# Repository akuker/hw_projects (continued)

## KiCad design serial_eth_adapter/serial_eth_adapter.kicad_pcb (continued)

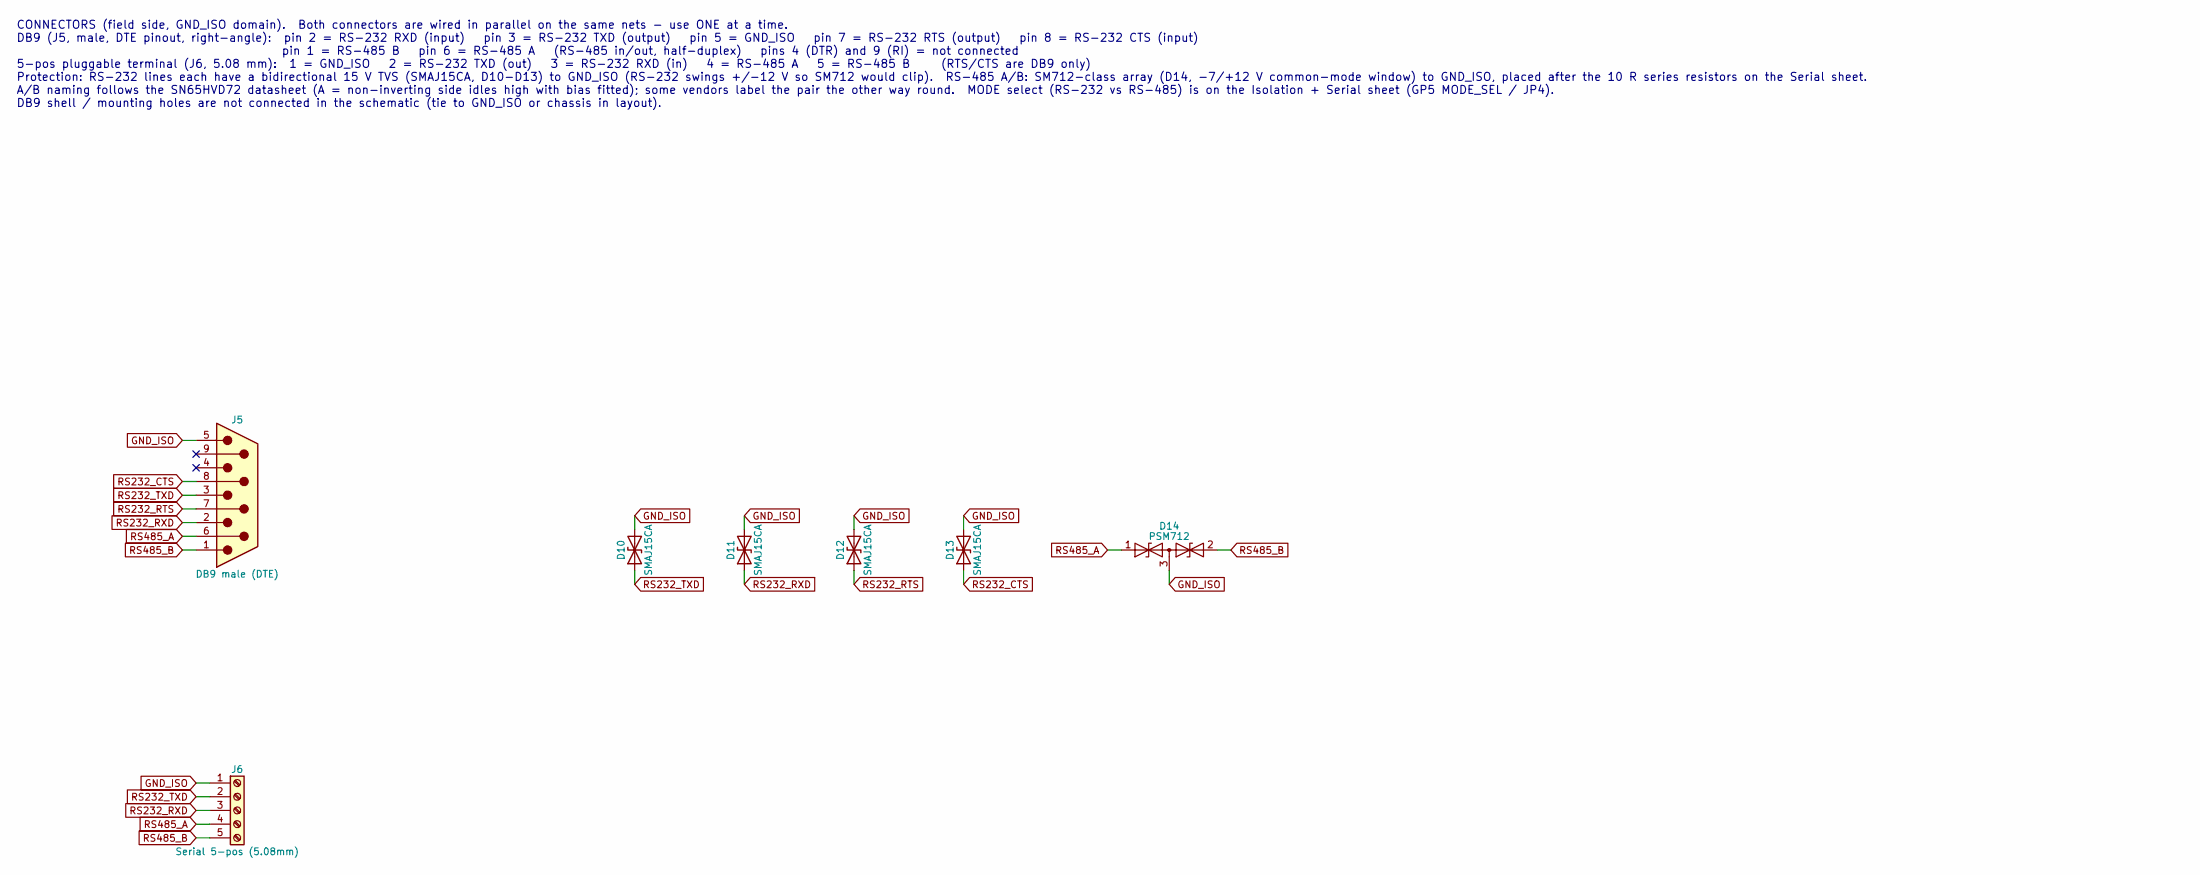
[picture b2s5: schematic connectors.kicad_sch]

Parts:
D10, D11, D12, D13: SMAJ15CA; D_SMA; MPN SMAJ15CA; LCSC C110044
D14: PSM712; SOT-23; MPN PSM712-LF-T7; LCSC C32677
J5: DB9 male (DTE); DSUB-9_Pins_Horizontal_P2.77x2.84mm_EdgePinOffset7.70mm_Hou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; MPN DS1037-09MNAKT74-0CC; LCSC C75750
J6: Serial 5-pos (5.08mm); PhoenixContact_MSTBA_2,5_5-G-5,08_1x05_P5.08mm_Horizontal; MPN KF2EDGR-5.08-5P; LCSC C441207

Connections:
GND_ISO: D10.2 (A2), D11.2 (A2), D12.2 (A2), D13.2 (A2), D14.3 (common), J5.5, J6.1; also elsewhere on the board
RS232_CTS: D13.1 (A1), J5.8; also elsewhere on the board
RS232_RTS: D12.1 (A1), J5.7; also elsewhere on the board
RS232_RXD: D11.1 (A1), J5.2, J6.3; also elsewhere on the board
RS232_TXD: D10.1 (A1), J5.3, J6.2; also elsewhere on the board
RS485_A: D14.1 (A1), J5.6, J6.4; also elsewhere on the board
RS485_B: D14.2 (A2), J5.1, J6.5; also elsewhere on the board

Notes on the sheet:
CONNECTORS (field side, GND_ISO domain). Both connectors are wired in parallel on the same nets - use ONE at a time. DB9 (J5, male, DTE pinout, right-angle): pin 2 = RS-232 RXD (input) pin 3 = RS-232 TXD (output) pin 5 = GND_ISO pin 7 = RS-232 RTS (output) pin 8 = RS-232 CTS (input) pin 1 = RS-485 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

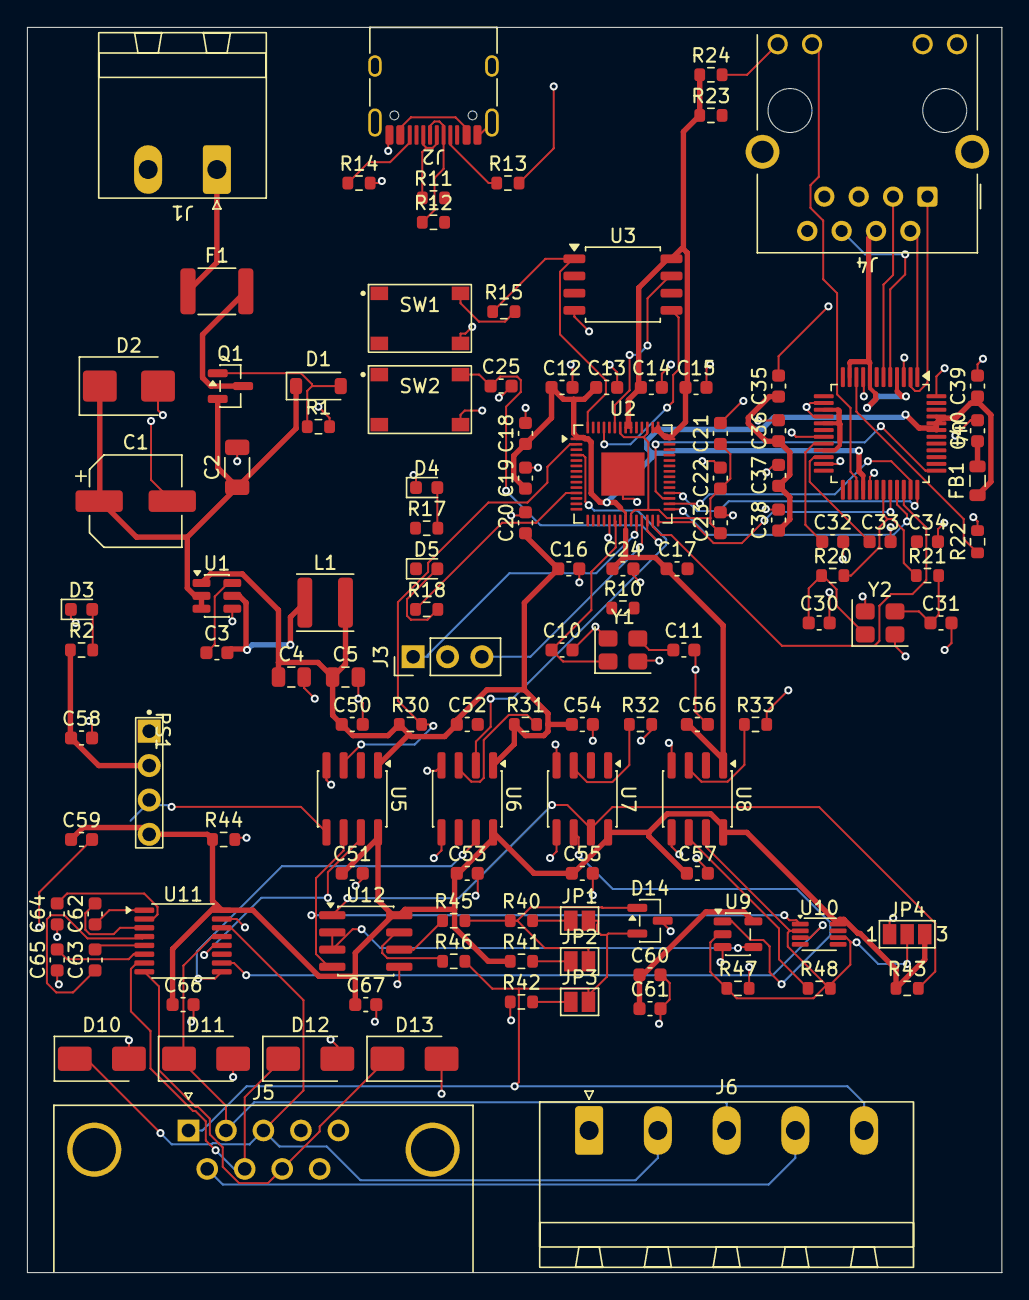
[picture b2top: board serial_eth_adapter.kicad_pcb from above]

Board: 2 copper layers, 72.0 x 92.0 mm, 119 parts (0 on the bottom side), 93 nets.

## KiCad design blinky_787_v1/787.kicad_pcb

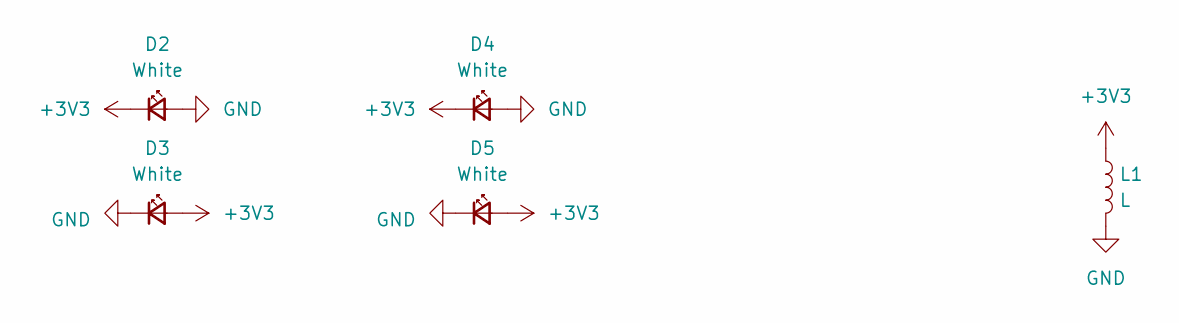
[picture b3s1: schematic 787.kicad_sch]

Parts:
D2, D3, D4, D5: White; LED_0603_1608Metric; LCSC C2290
L1: L; Coil based on ID 6

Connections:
+3V3: D2.1 (K), D3.2 (A), D4.1 (K), D5.2 (A), L1.1
GND: D2.2 (A), D3.1 (K), D4.2 (A), D5.1 (K), L1.2

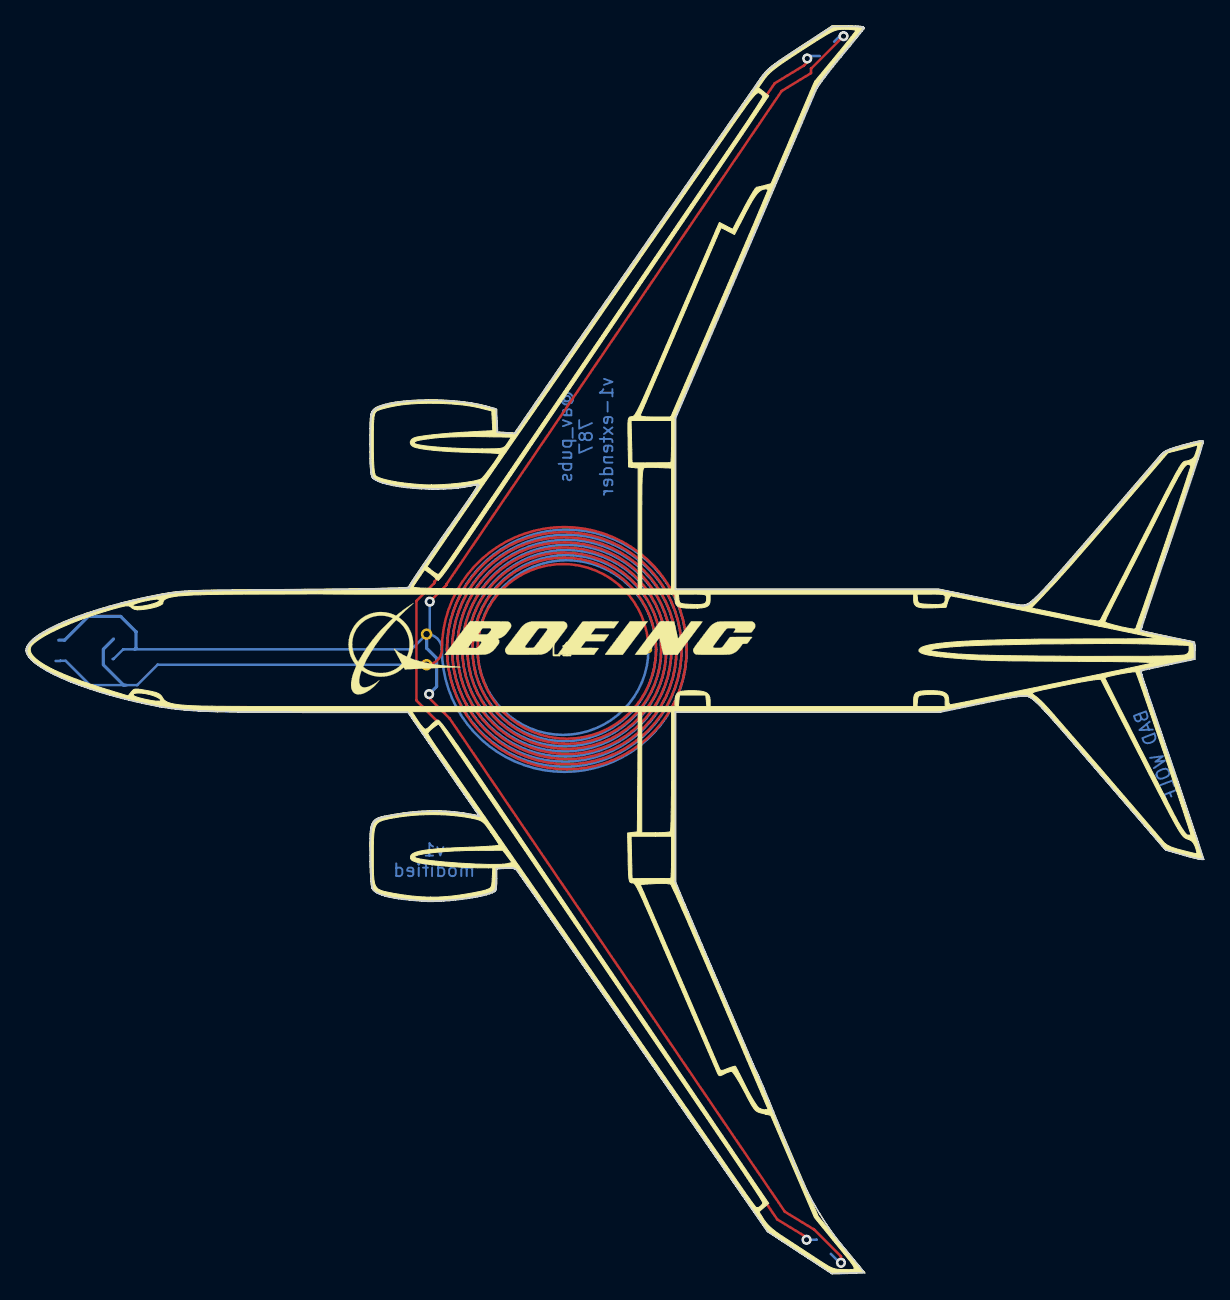
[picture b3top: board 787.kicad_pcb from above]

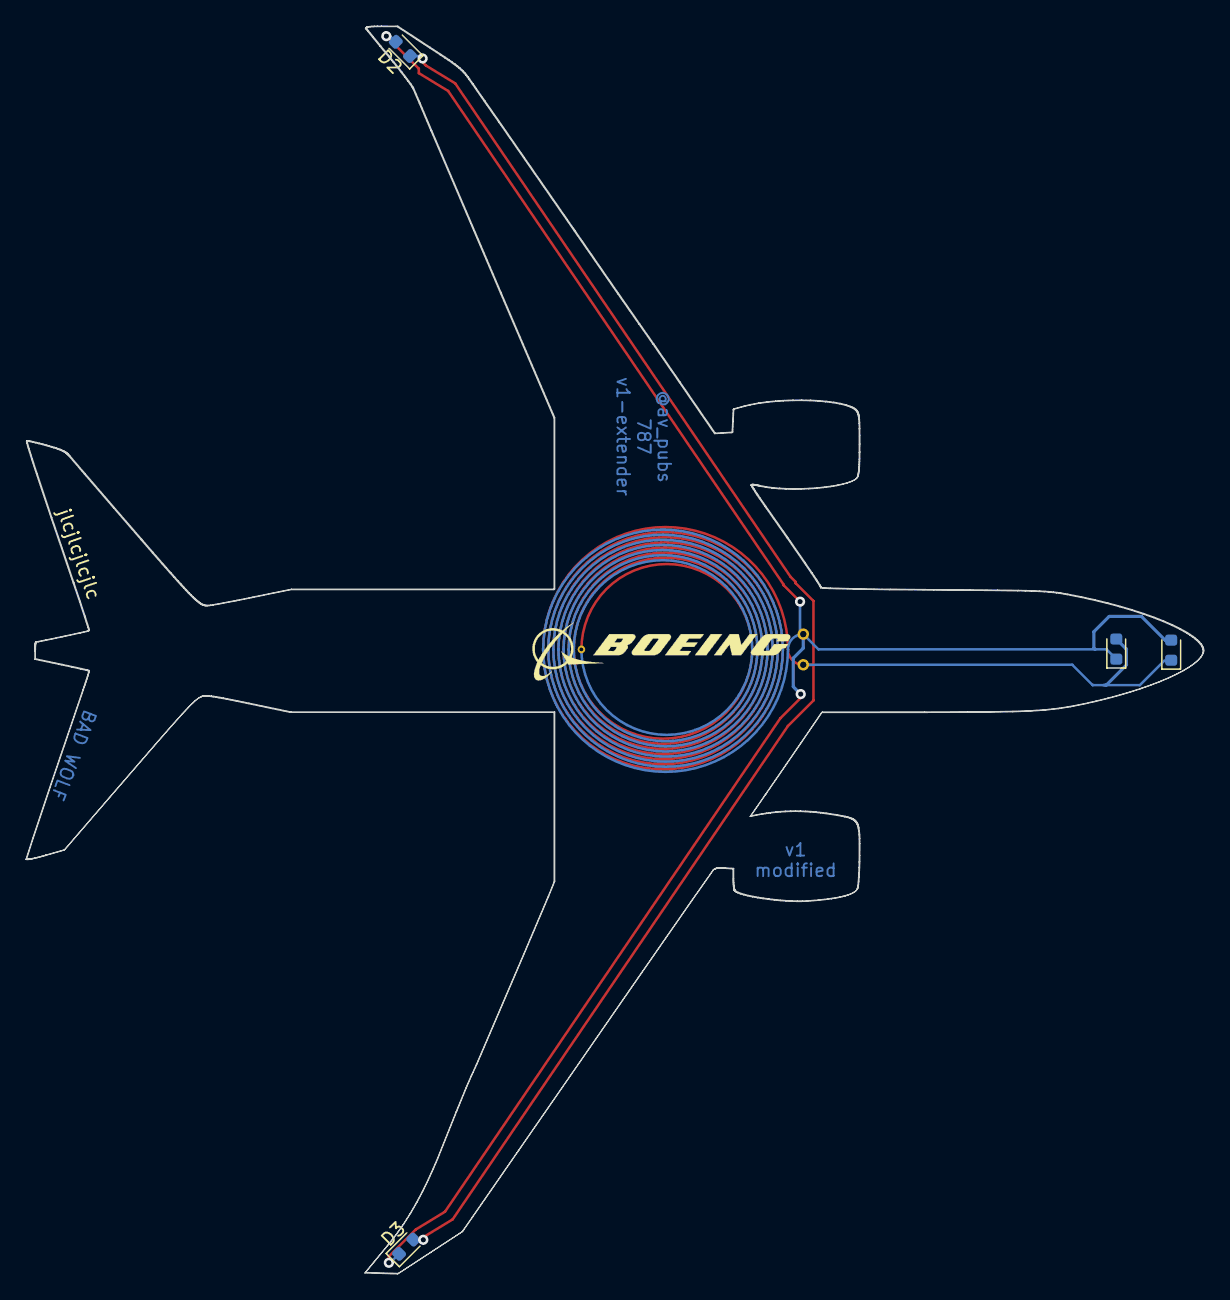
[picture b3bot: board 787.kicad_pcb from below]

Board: 2 copper layers, 92.3 x 97.8 mm, 5 parts (4 on the bottom side), 2 nets.

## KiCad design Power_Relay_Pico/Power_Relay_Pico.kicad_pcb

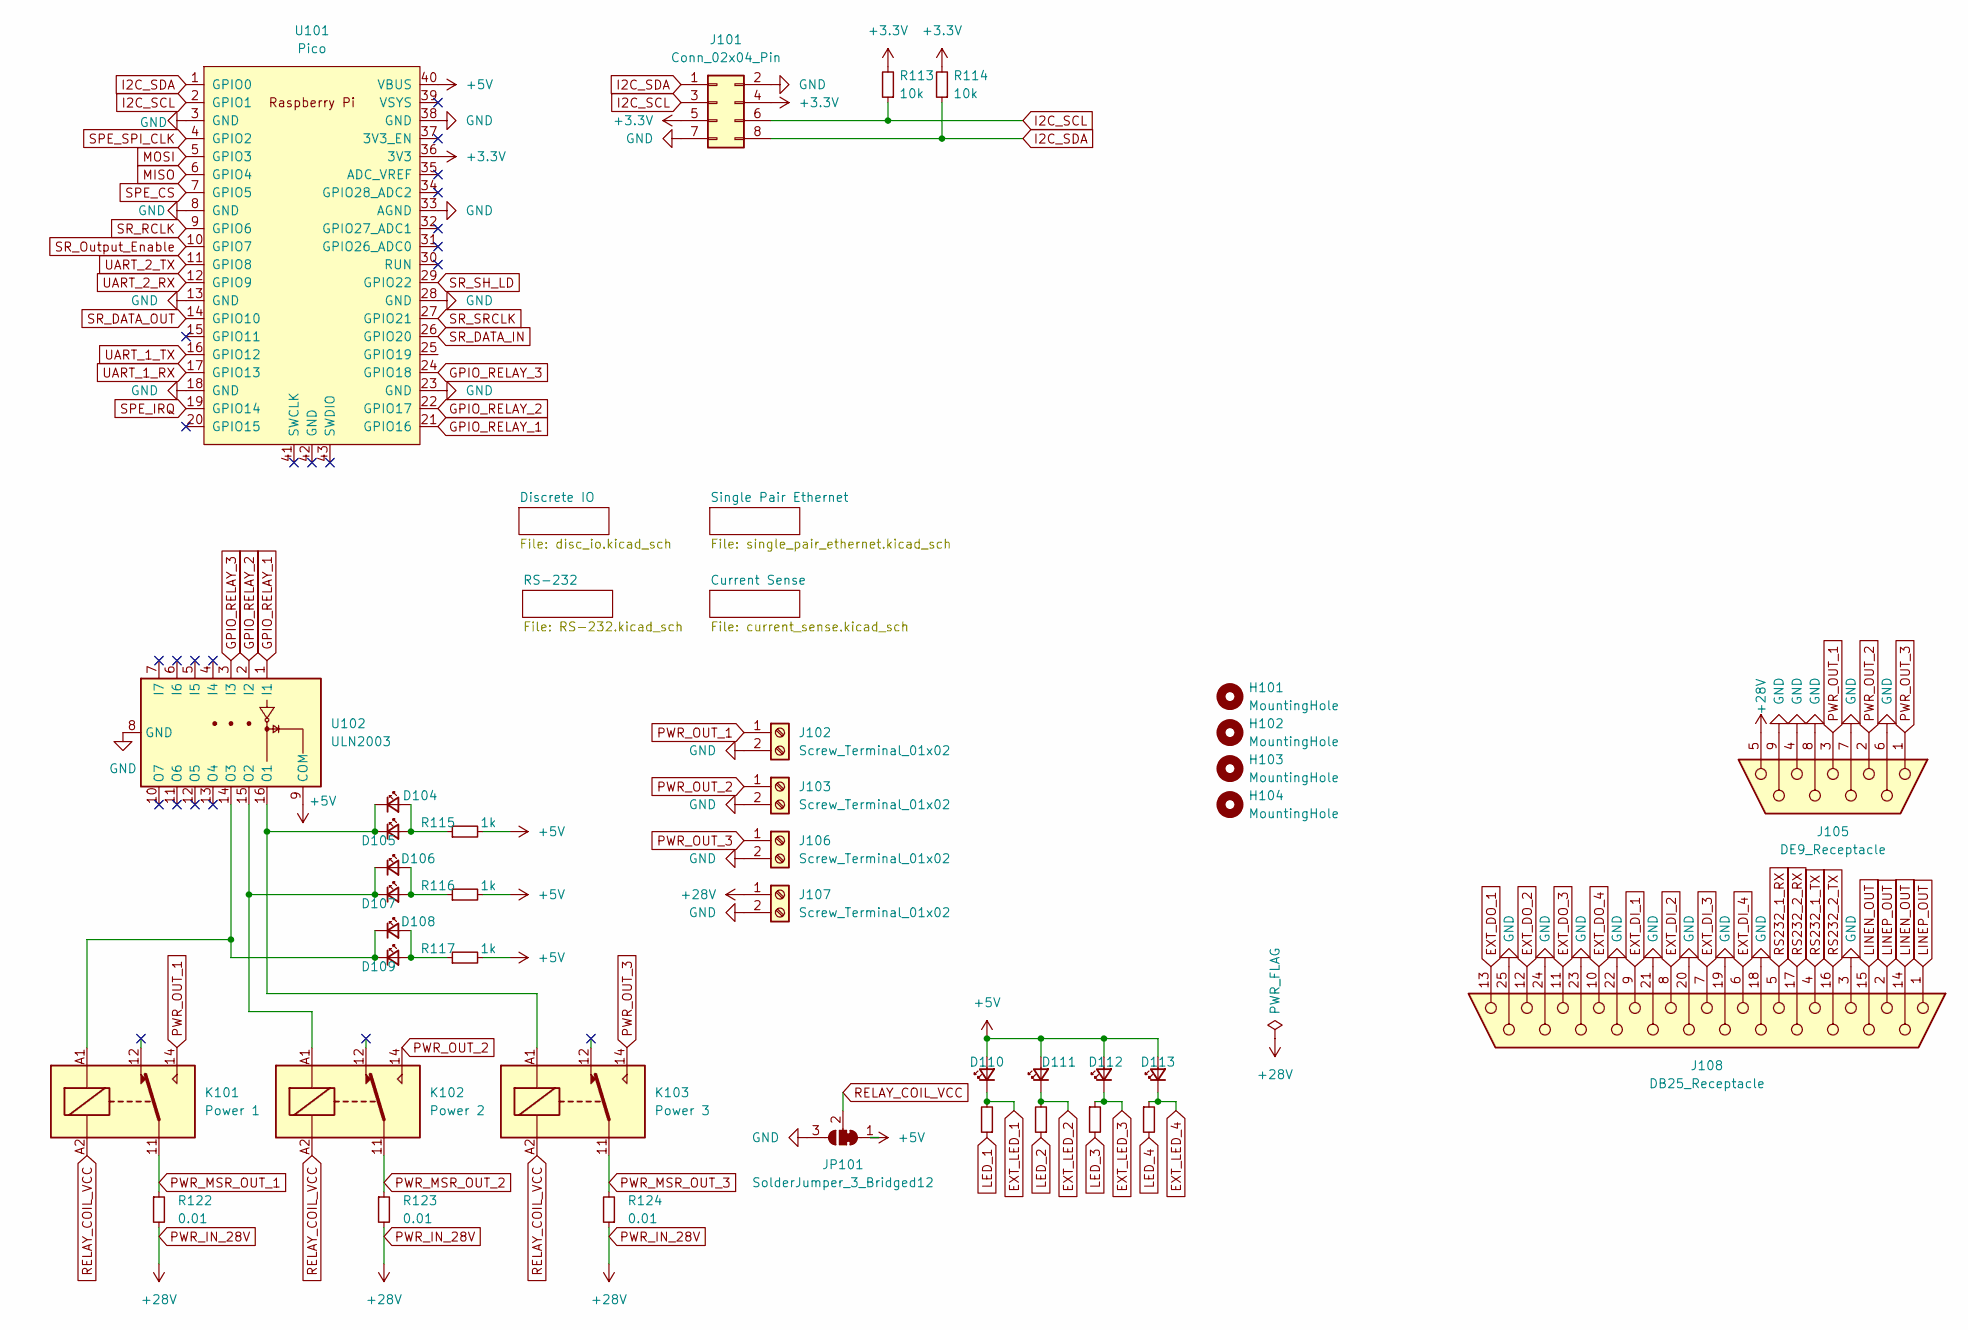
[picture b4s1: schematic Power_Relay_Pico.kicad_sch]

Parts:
D104, D106, D108: LED_Small; LED_0805_2012Metric; LCSC C2297
D105, D107, D109, D110, D111, D112, D113: LED_Small; LED_D3.0mm; LCSC --
H101, H102, H103, H104: MountingHole; MountingHole_3.2mm_M3; LCSC --
J101: Conn_02x04_Pin; PinHeader_2x04_P2.54mm_Vertical; LCSC --
J102, J103, J106, J107: Screw_Terminal_01x02; TerminalBlock_Xinya_XY308-2.54-2P_1x02_P2.54mm_Horizontal; LCSC --
J105: DE9_Receptacle; DSUB-9_Female_EdgeMount_P2.77mm; LCSC --
J108: DB25_Receptacle; DSUB-25_Female_EdgeMount_P2.77mm; LCSC --
JP101: SolderJumper_3_Bridged12; SolderJumper-3_P1.3mm_Bridged12_RoundedPad1.0x1.5mm; LCSC --
K101: Power 1; Relay_SPDT_Hongfa_HF3F-L-xx-1ZL1T; LCSC --
K102: Power 2; Relay_SPDT_Hongfa_HF3F-L-xx-1ZL1T; LCSC --
K103: Power 3; Relay_SPDT_Hongfa_HF3F-L-xx-1ZL1T; LCSC --
R113, R114: 10k; R_0603_1608Metric; LCSC C25804
R115, R116, R117, R118, R119, R120, R121: 1k; R_0603_1608Metric; LCSC C21190
R122, R123, R124: 0.01; R_1206_3216Metric; LCSC C105362
U101: Pico; RPi_Pico_SMD_TH; LCSC --
U102: ULN2003; SOIC-16_3.9x9.9mm_P1.27mm; LCSC C7512

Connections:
+3.3V: J101.4, J101.5, R113.2, R114.2, U101.36 (3V3); also elsewhere on the board
+5V: D110.2 (A), D111.2 (A), D112.2 (A), D113.2 (A), JP101.1 (A), R115.2, R116.2, R117.2, U101.40 (VBUS), U102.9 (COM); also elsewhere on the board
EXT_DI_1: J108.9; also elsewhere on the board
EXT_DI_2: J108.8; also elsewhere on the board
EXT_DI_3: J108.7; also elsewhere on the board
EXT_DI_4: J108.6; also elsewhere on the board
EXT_DO_1: J108.13; also elsewhere on the board
EXT_DO_2: J108.12; also elsewhere on the board
EXT_DO_3: J108.11; also elsewhere on the board
EXT_DO_4: J108.10; also elsewhere on the board
EXT_LED_1: D110.1 (K), R118.2
EXT_LED_2: D111.1 (K), R119.2
EXT_LED_3: D112.1 (K), R120.1
EXT_LED_4: D113.1 (K), R121.1
GND: J101.2, J101.7, J102.2, J103.2, J105.4, J105.6, J105.7, J105.8, J105.9, J106.2, J107.2, J108.3, J108.18, J108.19, J108.20, J108.21, J108.22, J108.23, J108.24, J108.25, JP101.3 (B), U101.3 (GND), U101.8 (GND), U101.13 (GND), U101.18 (GND), U101.23 (GND), U101.28 (GND), U101.33 (AGND), U101.38 (GND), U102.8 (GND); also elsewhere on the board
GPIO_RELAY_1: U101.21 (GPIO16), U102.1 (I1)
GPIO_RELAY_2: U101.22 (GPIO17), U102.2 (I2)
GPIO_RELAY_3: U101.24 (GPIO18), U102.3 (I3)
I2C_SCL: J101.3, J101.6, R113.1, U101.2 (GPIO1); also elsewhere on the board
I2C_SDA: J101.1, J101.8, R114.1, U101.1 (GPIO0); also elsewhere on the board
LED_1: R118.1; also elsewhere on the board
LED_2: R119.1; also elsewhere on the board
LED_3: R120.2; also elsewhere on the board
LED_4: R121.2; also elsewhere on the board
LINEN_OUT: J108.14, J108.15; also elsewhere on the board
LINEP_OUT: J108.1, J108.2; also elsewhere on the board
MISO: U101.6 (GPIO4); also elsewhere on the board
MOSI: U101.5 (GPIO3); also elsewhere on the board
unnamed: D104.2 (A), D105.2 (A), R115.1
unnamed: D104.1 (K), D105.1 (K), K103.A1, U102.16 (O1)
unnamed: D106.2 (A), D107.2 (A), R116.1
unnamed: D106.1 (K), D107.1 (K), K102.A1, U102.15 (O2)
unnamed: D108.2 (A), D109.2 (A), R117.1
unnamed: D108.1 (K), D109.1 (K), K101.A1, U102.14 (O3)
PWR_IN_28V: J105.5, J107.1, R122.2, R123.2, R124.1; also elsewhere on the board
PWR_MSR_OUT_1: K101.11, R122.1; also elsewhere on the board
PWR_MSR_OUT_2: K102.11, R123.1; also elsewhere on the board
PWR_MSR_OUT_3: K103.11, R124.2; also elsewhere on the board
PWR_OUT_1: J102.1, J105.3, K101.14
PWR_OUT_2: J103.1, J105.2, K102.14
PWR_OUT_3: J105.1, J106.1, K103.14
RELAY_COIL_VCC: JP101.2 (C), K101.A2, K102.A2, K103.A2
RS232_1_RX: J108.5; also elsewhere on the board
RS232_1_TX: J108.4; also elsewhere on the board
RS232_2_RX: J108.17; also elsewhere on the board
RS232_2_TX: J108.16; also elsewhere on the board
SPE_CS: U101.7 (GPIO5); also elsewhere on the board
SPE_IRQ: U101.19 (GPIO14); also elsewhere on the board
SPE_SPI_CLK: U101.4 (GPIO2); also elsewhere on the board
SR_DATA_IN: U101.26 (GPIO20); also elsewhere on the board
SR_DATA_OUT: U101.14 (GPIO10); also elsewhere on the board
SR_Output_Enable: U101.10 (GPIO7); also elsewhere on the board
SR_RCLK: U101.9 (GPIO6); also elsewhere on the board
SR_SH_LD: U101.29 (GPIO22); also elsewhere on the board
SR_SRCLK: U101.27 (GPIO21); also elsewhere on the board
UART_1_RX: U101.17 (GPIO13); also elsewhere on the board
UART_1_TX: U101.16 (GPIO12); also elsewhere on the board
UART_2_RX: U101.12 (GPIO9); also elsewhere on the board
UART_2_TX: U101.11 (GPIO8); also elsewhere on the board

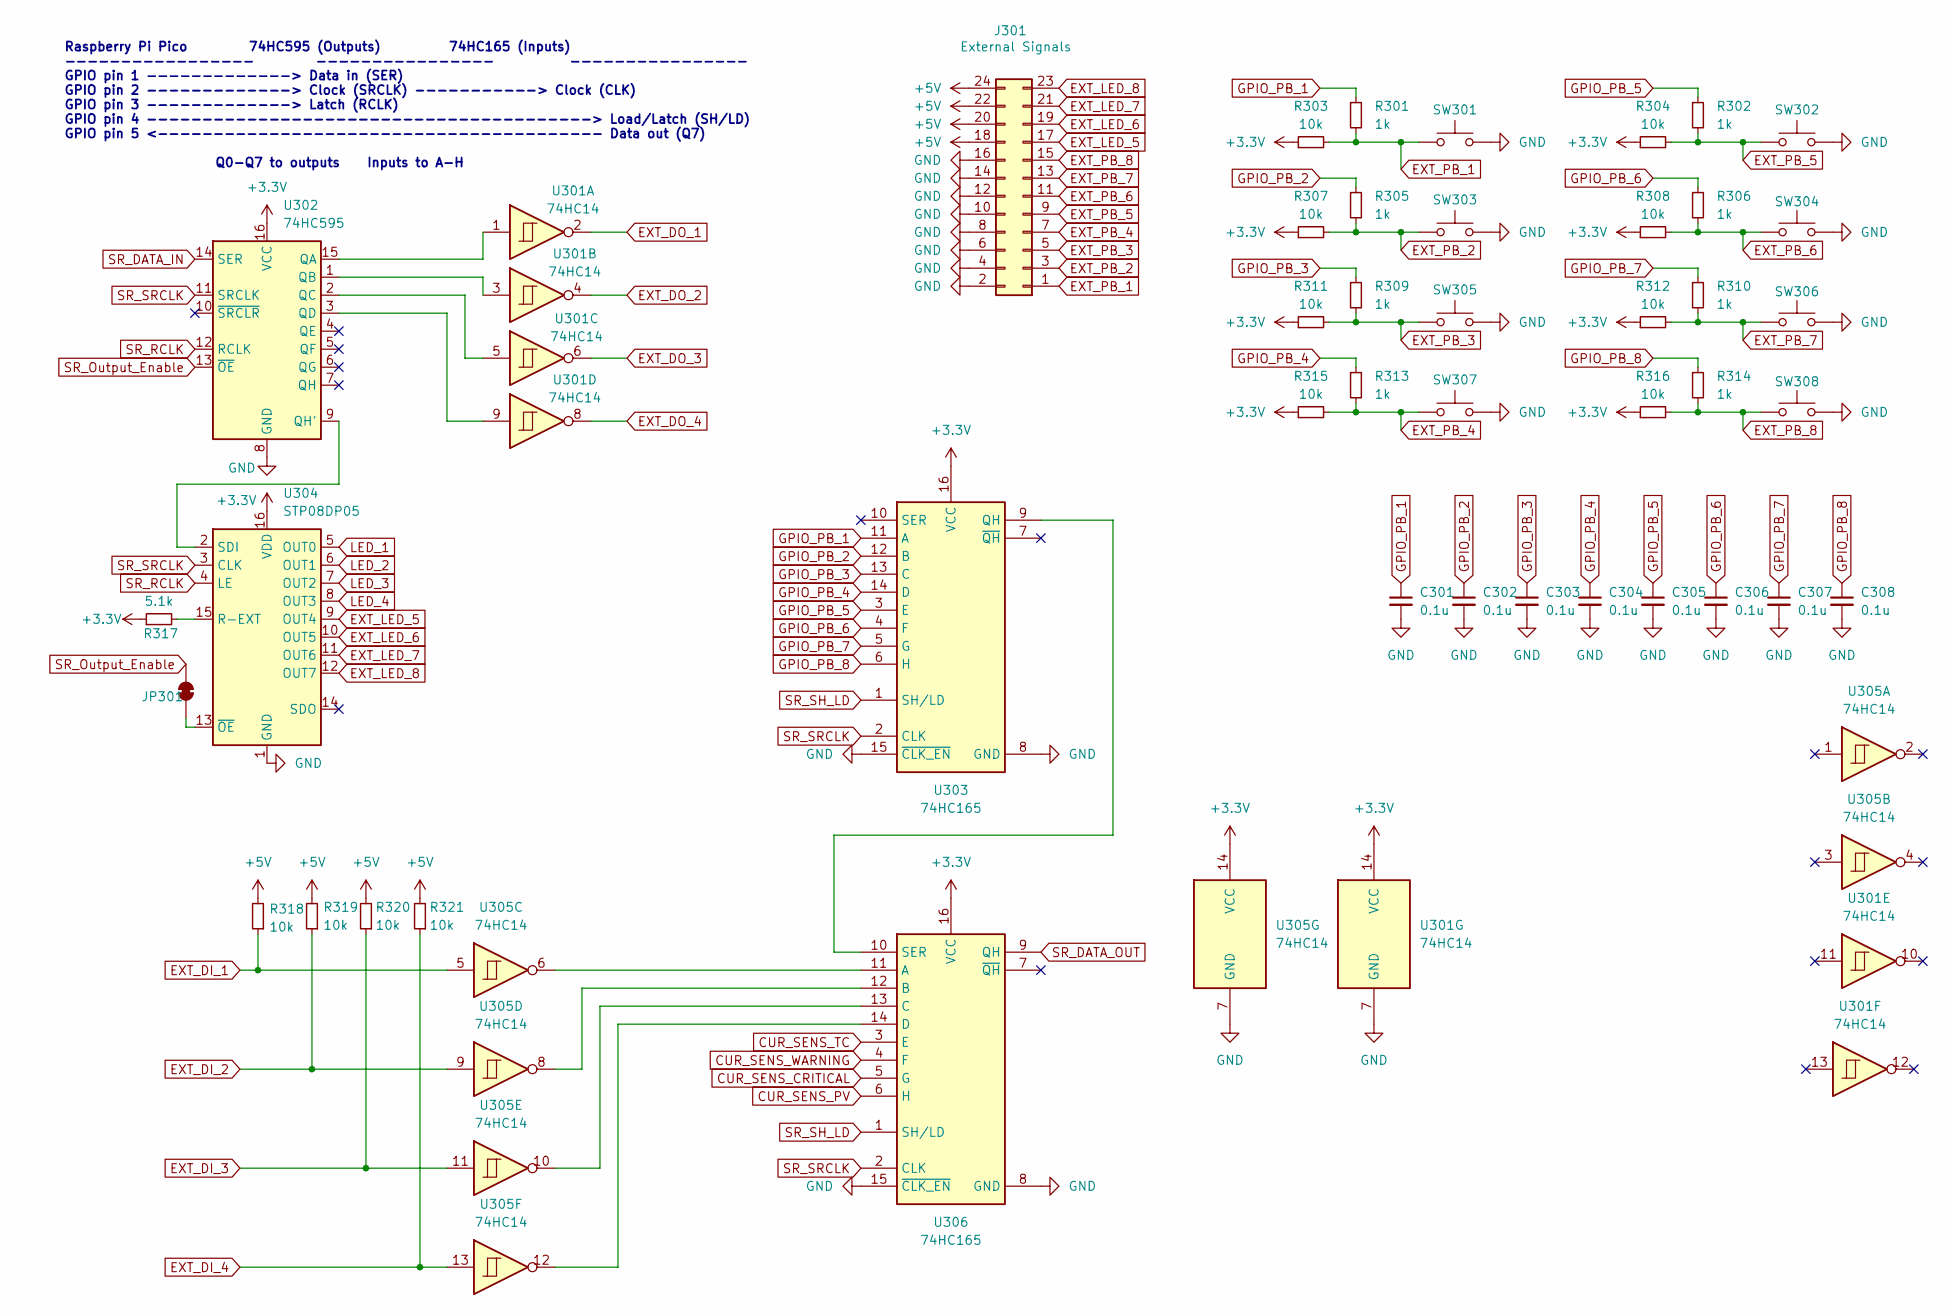
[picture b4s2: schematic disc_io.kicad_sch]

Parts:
C301, C302, C303, C304, C305, C306, C307, C308: 0.1u; C_0603_1608Metric; LCSC C14663
J301: External Signals; PinSocket_2x12_P2.54mm_Vertical; LCSC --
JP301: SolderJumper_2_Bridged; SolderJumper-2_P1.3mm_Bridged_RoundedPad1.0x1.5mm; LCSC --
R301, R302, R305, R306, R309, R310, R313, R314: 1k; R_0603_1608Metric; LCSC C21190
R303, R304, R307, R308, R311, R312, R315, R316, R318, R319, R320, R321: 10k; R_0603_1608Metric; LCSC C25804
R317: 5.1k; R_0603_1608Metric; LCSC C23186
SW301, SW302, SW303, SW304, SW305, SW306, SW307, SW308: SW_Push; SW_PUSH_6mm; LCSC --
U301, U305: 74HC14; SOIC-14_3.9x8.7mm_P1.27mm; LCSC C133541
U302: 74HC595; SOIC-16_3.9x9.9mm_P1.27mm; LCSC C5947
U303, U306: 74HC165; SOIC-16_3.9x9.9mm_P1.27mm; LCSC C5613
U304: STP08DP05; SOIC-16_3.9x9.9mm_P1.27mm; LCSC C157385

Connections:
+3.3V: R303.1, R304.1, R307.1, R308.1, R311.1, R312.1, R315.1, R316.1, R317.1, U301.14 (VCC), U302.16 (VCC), U303.16 (VCC), U304.16 (VDD), U305.14 (VCC), U306.16 (VCC); also elsewhere on the board
+5V: J301.18, J301.20, J301.22, J301.24, R318.2, R319.2, R320.2, R321.2; also elsewhere on the board
CUR_SENS_CRITICAL: U306.5 (G); also elsewhere on the board
CUR_SENS_PV: U306.6 (H); also elsewhere on the board
CUR_SENS_TC: U306.3 (E); also elsewhere on the board
CUR_SENS_WARNING: U306.4 (F); also elsewhere on the board
EXT_DI_1: R318.1, U305.5; also elsewhere on the board
EXT_DI_2: R319.1, U305.9; also elsewhere on the board
EXT_DI_3: R320.1, U305.11; also elsewhere on the board
EXT_DI_4: R321.1, U305.13; also elsewhere on the board
EXT_DO_1: U301.2; also elsewhere on the board
EXT_DO_2: U301.4; also elsewhere on the board
EXT_DO_3: U301.6; also elsewhere on the board
EXT_DO_4: U301.8; also elsewhere on the board
EXT_LED_5: J301.17, U304.9 (OUT4)
EXT_LED_6: J301.19, U304.10 (OUT5)
EXT_LED_7: J301.21, U304.11 (OUT6)
EXT_LED_8: J301.23, U304.12 (OUT7)
EXT_PB_1: J301.1, R301.2, R303.2, SW301.1
EXT_PB_2: J301.3, R305.2, R307.2, SW303.1
EXT_PB_3: J301.5, R309.2, R311.2, SW305.1
EXT_PB_4: J301.7, R313.2, R315.2, SW307.1
EXT_PB_5: J301.9, R302.2, R304.2, SW302.1
EXT_PB_6: J301.11, R306.2, R308.2, SW304.1
EXT_PB_7: J301.13, R310.2, R312.2, SW306.1
EXT_PB_8: J301.15, R314.2, R316.2, SW308.1
GND: C301.2, C302.2, C303.2, C304.2, C305.2, C306.2, C307.2, C308.2, J301.2, J301.4, J301.6, J301.8, J301.10, J301.12, J301.14, J301.16, SW301.2, SW302.2, SW303.2, SW304.2, SW305.2, SW306.2, SW307.2, SW308.2, U301.7 (GND), U302.8 (GND), U303.8 (GND), U303.15 (~CLK_EN), U304.1 (GND), U305.7 (GND), U306.8 (GND), U306.15 (~CLK_EN); also elsewhere on the board
GPIO_PB_1: C301.1, R301.1, U303.11 (A)
GPIO_PB_2: C302.1, R305.1, U303.12 (B)
GPIO_PB_3: C303.1, R309.1, U303.13 (C)
GPIO_PB_4: C304.1, R313.1, U303.14 (D)
GPIO_PB_5: C305.1, R302.1, U303.3 (E)
GPIO_PB_6: C306.1, R306.1, U303.4 (F)
GPIO_PB_7: C307.1, R310.1, U303.5 (G)
GPIO_PB_8: C308.1, R314.1, U303.6 (H)
LED_1: U304.5 (OUT0); also elsewhere on the board
LED_2: U304.6 (OUT1); also elsewhere on the board
LED_3: U304.7 (OUT2); also elsewhere on the board
LED_4: U304.8 (OUT3); also elsewhere on the board
unnamed: JP301.1 (A), U304.13 (~OE)
unnamed: U301.1, U302.15 (QA)
unnamed: U301.3, U302.1 (QB)
unnamed: U301.5, U302.2 (QC)
unnamed: U301.9, U302.3 (QD)
unnamed: U302.9 (QH'), U304.2 (SDI)
unnamed: U303.9 (QH), U306.10 (SER)
unnamed: R317.2, U304.15 (R-EXT)
unnamed: U305.6, U306.11 (A)
unnamed: U305.8, U306.12 (B)
unnamed: U305.10, U306.13 (C)
unnamed: U305.12, U306.14 (D)
SR_DATA_IN: U302.14 (SER); also elsewhere on the board
SR_DATA_OUT: U306.9 (QH); also elsewhere on the board
SR_Output_Enable: JP301.2 (B), U302.13 (~OE); also elsewhere on the board
SR_RCLK: U302.12 (RCLK), U304.4 (LE); also elsewhere on the board
SR_SH_LD: U303.1 (SH/LD), U306.1 (SH/LD); also elsewhere on the board
SR_SRCLK: U302.11 (SRCLK), U303.2 (CLK), U304.3 (CLK), U306.2 (CLK); also elsewhere on the board

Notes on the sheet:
Raspberry Pi Pico 74HC595 (Outputs) 74HC165 (Inputs) ----------------- ---------------- ---------------- GPIO pin 1 -------------> Data in (SER) GPIO pin 2 -------------> Clock (SRCLK) -----------> Clock (CLK) GPIO pin 3 -------------> Latch (RCLK) GPIO pin 4 ---------------------------------------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

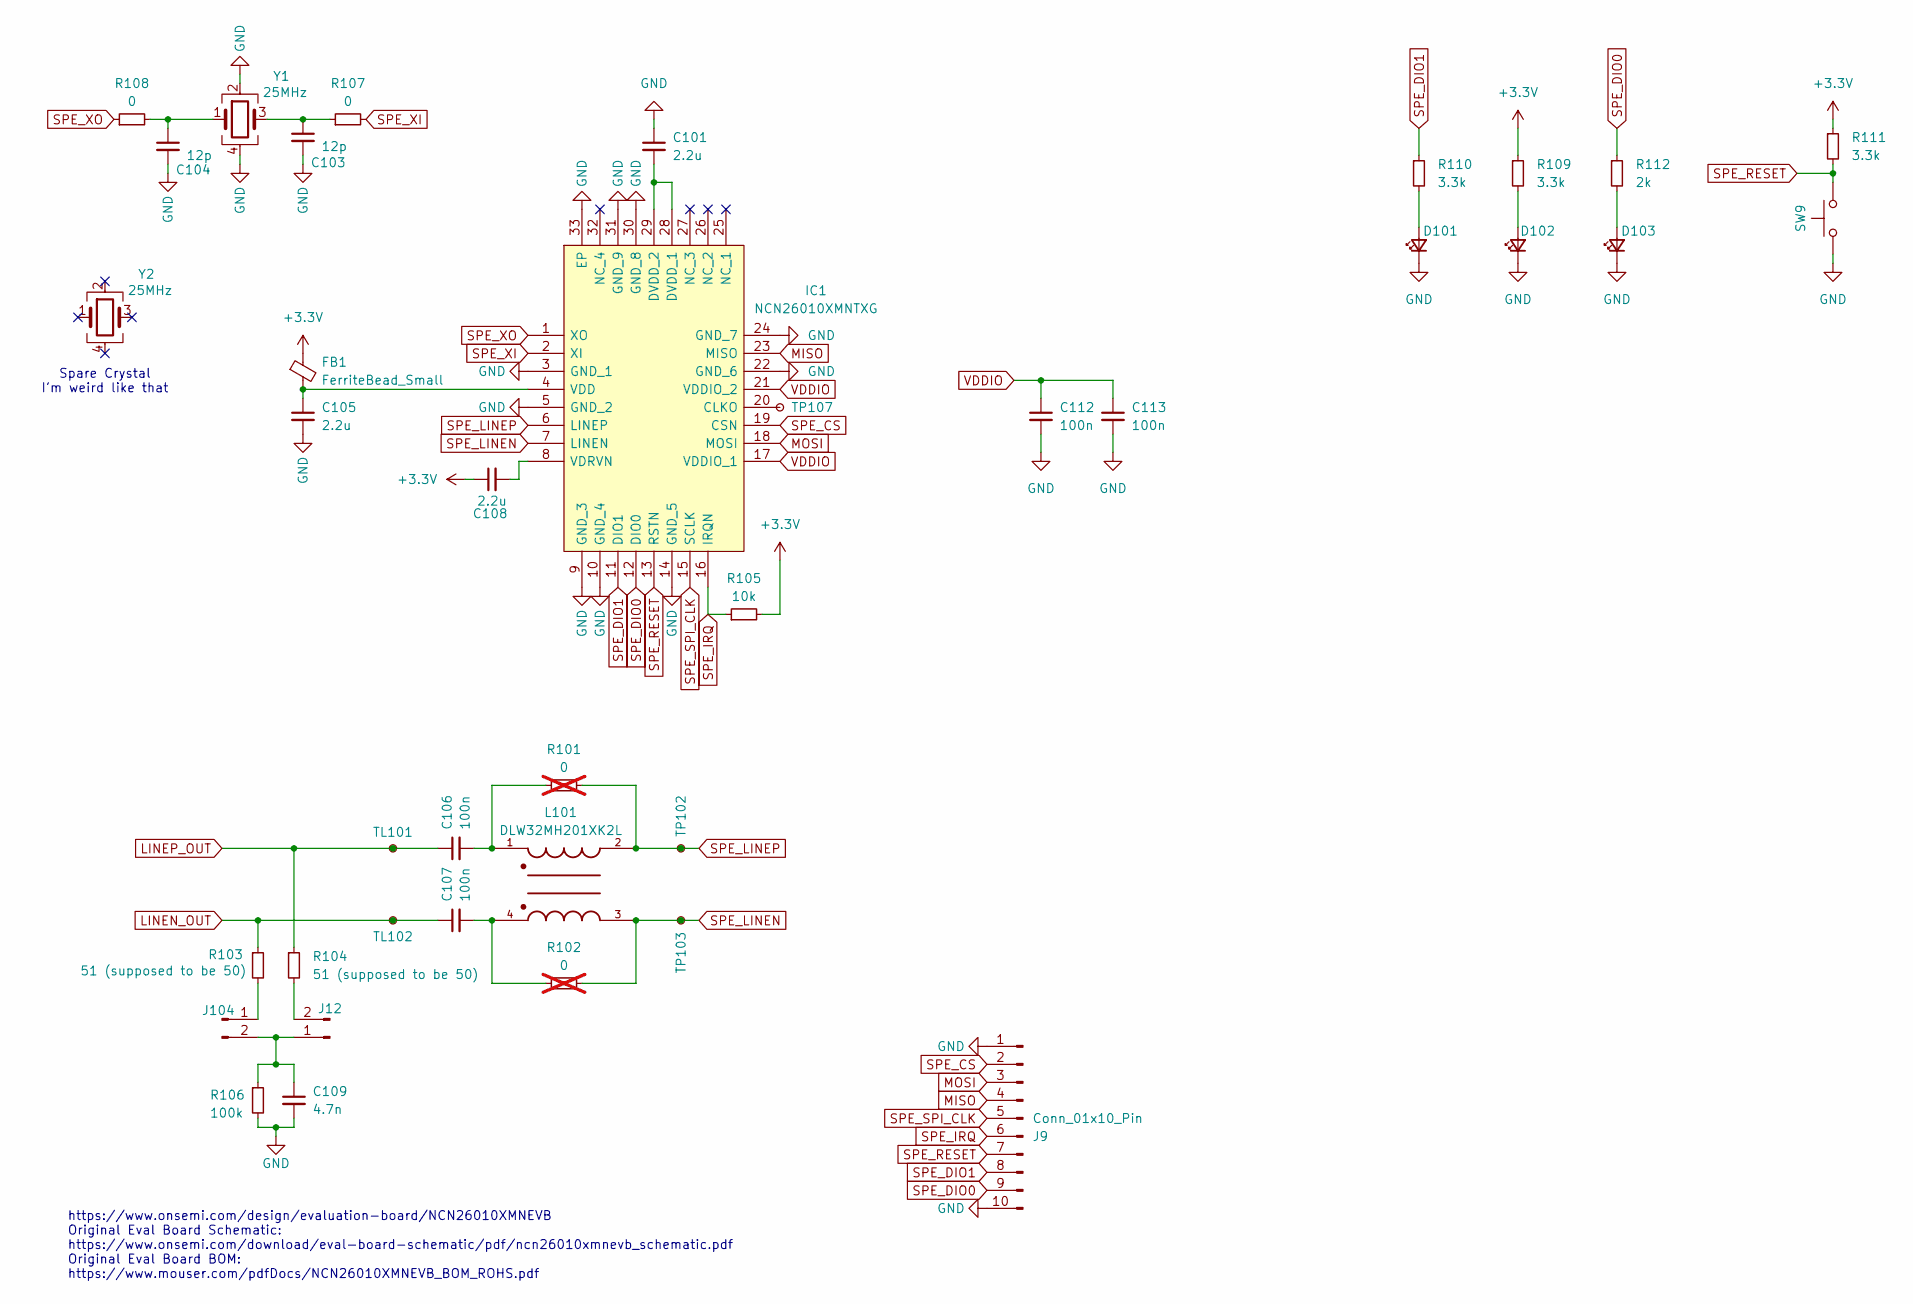
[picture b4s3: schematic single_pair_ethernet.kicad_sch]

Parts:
C101, C105, C108: 2.2u; C_0603_1608Metric; LCSC C23630
C103, C104: 12p; C_0603_1608Metric; LCSC C38523
C106, C107, C112, C113: 100n; C_0603_1608Metric; LCSC C14663
C109: 4.7n; C_0603_1608Metric; LCSC C53987
D101, D102, D103: LED_Small; LED_0805_2012Metric; LCSC C2297
FB1: FerriteBead_Small; L_0805_2012Metric; LCSC C1017
IC1: NCN26010XMNTXG; Manufacturer_Part_Number NCN26010XMNTXG; Mouser Part Number 863-NCN26010XMNTXG
J9: Conn_01x10_Pin; PinHeader_1x10_P2.54mm_Vertical; LCSC --
J12, J104: Conn_01x02_Pin; PinHeader_1x02_P2.54mm_Vertical; LCSC --
L101: DLW32MH201XK2L; FIL_DLW32MH201XK2L; LCSC C883600
R101, R102: 0; R_0603_1608Metric; LCSC C21189; not fitted
R103, R104: 51 (supposed to be 50); R_0603_1608Metric; LCSC C23197
R105: 10k; R_0603_1608Metric; LCSC C25804
R106: 100k; R_0603_1608Metric; LCSC C25803
R107, R108: 0; R_0603_1608Metric; LCSC C21189
R109, R110, R111: 3.3k; R_0603_1608Metric; LCSC C22978
R112: 2k; R_0603_1608Metric; LCSC C22975
SW9: SW_Push; SW_PUSH_6mm; LCSC --
TL101, TL102: TestPoint_Small; TestPoint_Loop_D2.50mm_Drill1.0mm; LCSC --
TP102, TP103, TP107: TestPoint_Small; TestPoint_Pad_D1.0mm; LCSC --
Y1, Y2: 25MHz; Crystal_SMD_3225-4Pin_3.2x2.5mm; LCSC C9006

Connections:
+3.3V: C108.1, FB1.1, R105.2, R109.1, R111.1; also elsewhere on the board
GND: C101.1, C103.2, C104.2, C105.2, C109.2, C112.2, C113.2, D101.1 (K), D102.1 (K), D103.1 (K), IC1.3 (GND_1), IC1.5 (GND_2), IC1.9 (GND_3), IC1.10 (GND_4), IC1.14 (GND_5), IC1.22 (GND_6), IC1.24 (GND_7), IC1.30 (GND_8), IC1.31 (GND_9), IC1.33 (EP), J9.1, J9.10, R106.2, SW9.1, Y1.2, Y1.4; also elsewhere on the board
LINEN_OUT: C107.1, R103.1, TL102.1; also elsewhere on the board
LINEP_OUT: C106.1, R104.1, TL101.1; also elsewhere on the board
MISO: IC1.23 (MISO), J9.4; also elsewhere on the board
MOSI: IC1.18 (MOSI), J9.3; also elsewhere on the board
unnamed: C103.1, R107.1, Y1.3
unnamed: C104.1, R108.2, Y1.1
unnamed: C106.2, L101.1, R101.1
unnamed: C107.2, L101.4, R102.1
unnamed: D101.2 (A), R110.2
unnamed: D102.2 (A), R109.2
unnamed: D103.2 (A), R112.2
unnamed: IC1.20 (CLKO), TP107.1
unnamed: C101.2, IC1.28 (DVDD_1), IC1.29 (DVDD_2)
unnamed: C105.1, FB1.2, IC1.4 (VDD)
unnamed: C108.2, IC1.8 (VDRVN)
unnamed: J12.2, R104.2
unnamed: J104.1, R103.2
unnamed: C109.1, J12.1, J104.2, R106.1
SPE_CS: IC1.19 (CSN), J9.2; also elsewhere on the board
SPE_DIO0: IC1.12 (DIO0), J9.9, R112.1
SPE_DIO1: IC1.11 (DIO1), J9.8, R110.1
SPE_IRQ: IC1.16 (IRQN), J9.6, R105.1; also elsewhere on the board
SPE_LINEN: IC1.7 (LINEN), L101.3, R102.2, TP103.1
SPE_LINEP: IC1.6 (LINEP), L101.2, R101.2, TP102.1
SPE_RESET: IC1.13 (RSTN), J9.7, R111.2, SW9.2
SPE_SPI_CLK: IC1.15 (SCLK), J9.5; also elsewhere on the board
SPE_XI: IC1.2 (XI), R107.2
SPE_XO: IC1.1 (XO), R108.1
VDDIO: C112.1, C113.1, IC1.17 (VDDIO_1), IC1.21 (VDDIO_2)

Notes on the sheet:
Spare Crystal I'm weird like that
https://www.onsemi.com/design/evaluation-board/NCN26010XMNEVB Original Eval Board Schematic: https://www.onsemi.com/download/eval-board-schematic/pdf/ncn26010xmnevb_schematic.pdf Original Eval Board BOM: https://www.mouser.com/pdfDocs/NCN26010XMNEVB_BOM_ROHS.pdf
